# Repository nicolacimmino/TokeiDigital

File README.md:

# TokeiDigital

TokeiDigital [to̞ke̞ːdigital] is a line of clocks for geeks, nerds, and makers that come in a kit to assemble. The clock faces are unconventional and, true to the spirit of this project, always abound with colorful, blinking lights. These clocks are for you if:

* You believe a UART is a cool interface to setup a clock.
* You believe setting registers HEX values in a terminal is a good way to change LED colors and tweak settings.
* You believe a clock that just shows time with two hands is boring.

All models come with full schematics, PBCs, source code and all tools needed to program the clock. The project is OSHWA certified (PL000019).

Additionally you can buy them as kits ready to assemble on Tindie: https://www.tindie.com/stores/nicola_cimmino/

### Models

|Model|Description|Time|Date|DST|LEDs|Movement|
|-----|-----------|--------|----|---|----|----|
| [TD-FBUH01](board/TD-FBUH01) |Reproduction of the iconic Berlin Uhr.|X||X*1|36 RGB|TD-M5037|
| [TD-FDCF01](board/TD-FDCF01) |60 LEDs display time encoded as DCF77 bitstream.|X|X|X|60 RGB|TD-M5037|

<sub>*1) How can DST work if there's no date? The movment, internally, tracks the date, but the clock face doesn't have LEDs to show it. For DST Auto to work correctly you will need to set the date using the serial interface.</sub>

### Movements

|Model|Description|UART|Backup<br>Battery|W (mm)|H (mm)|
|-----|-----------|--------|----|---|----|
| [TD-M5037](board/TD-M5037)|Basic but powerful movement.|X|CR2032|50|37|

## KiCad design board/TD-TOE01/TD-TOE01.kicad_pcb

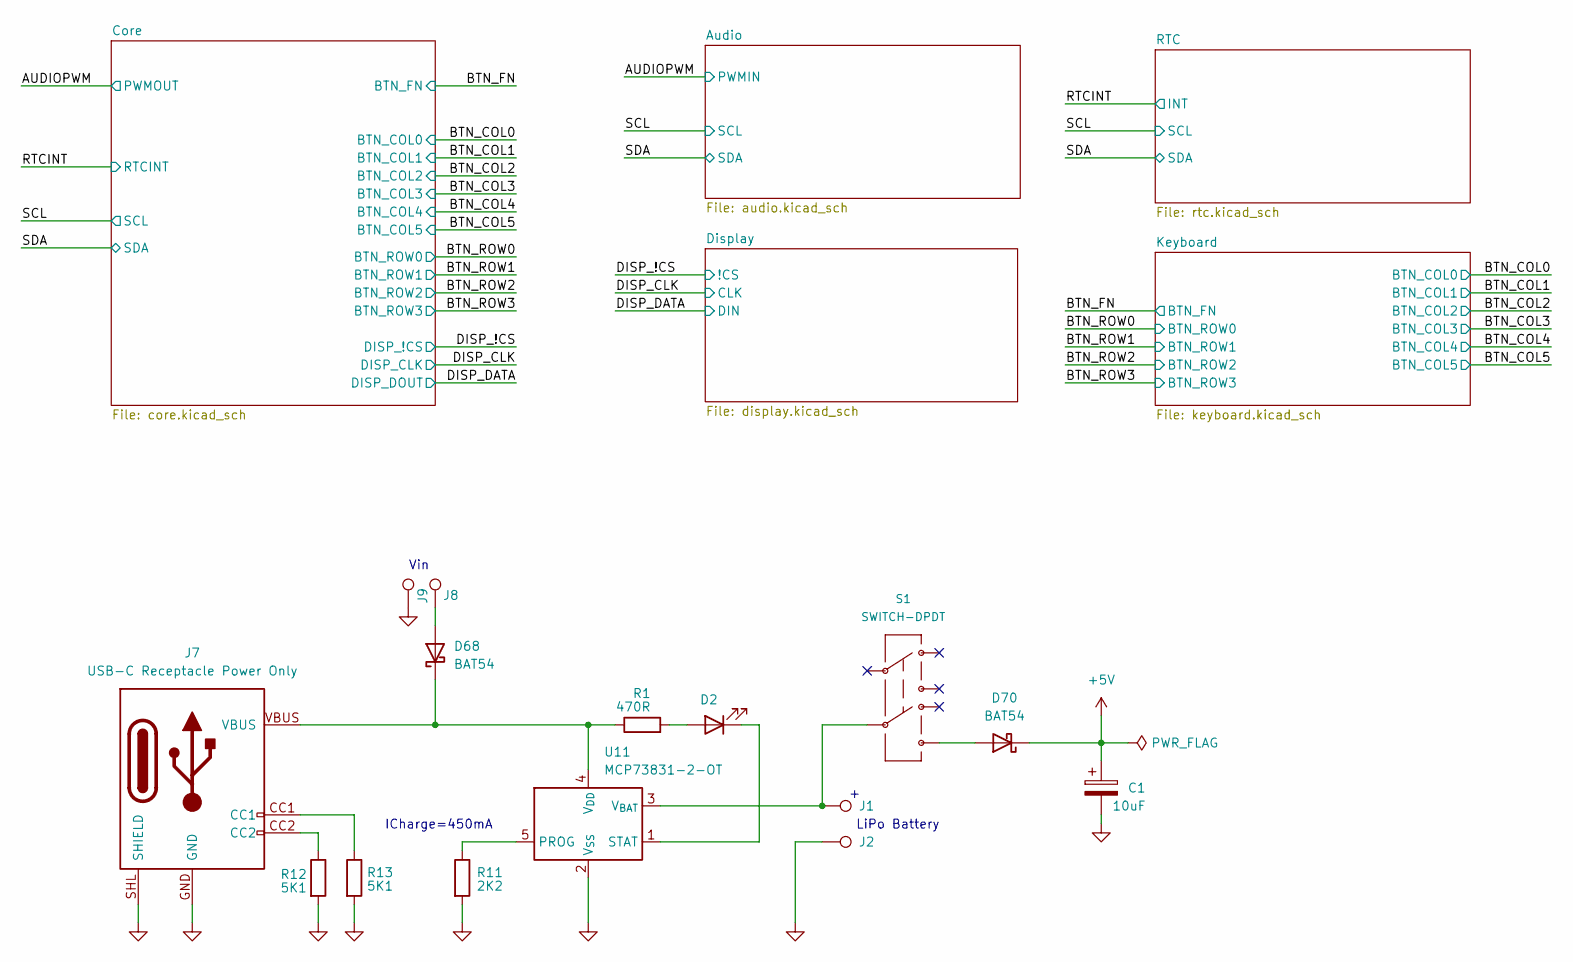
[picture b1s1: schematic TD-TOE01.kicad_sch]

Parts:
C1: 10uF; C_1206
D2: LED1206; LED_1206_3216Metric
D68, D70: BAT54; TSOT-23
J1, J8: BAT+; Power Pin
J2, J9: BAT-; Power Pin
J7: USB-C Receptacle Power Only; AMPHENOL_12402012E212A
R1: 470R; R_0805
R11: 2K2; R_0805
R12, R13: 5K1; R_0805
S1: SWITCH-DPDT; SW_DPDT_SMD_MINI
U11: MCP73831-2-OT; SOT-23-5

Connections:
+5V: C1.1, D70.3 (K); also elsewhere on the board
GND: C1.2, J2.1, J7.GND, J7.SHL (SHIELD), J9.1, R11.2, R12.2, R13.2, U11.2 (V_{SS}); also elsewhere on the board
unnamed: D2.2 (A), R1.2
unnamed: D2.1 (K), U11.1 (STAT)
unnamed: D68.1 (A), J8.1
unnamed: D68.3 (K), J7.VBUS, R1.1, U11.4 (V_{DD})
unnamed: D70.1 (A), S1.6
unnamed: J7.CC1, R13.1
unnamed: J7.CC2, R12.1
unnamed: R11.1, U11.5 (PROG)
unnamed: J1.1, S1.5, U11.3 (V_{BAT})

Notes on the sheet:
Vin
ICharge=450mA
LiPo Battery

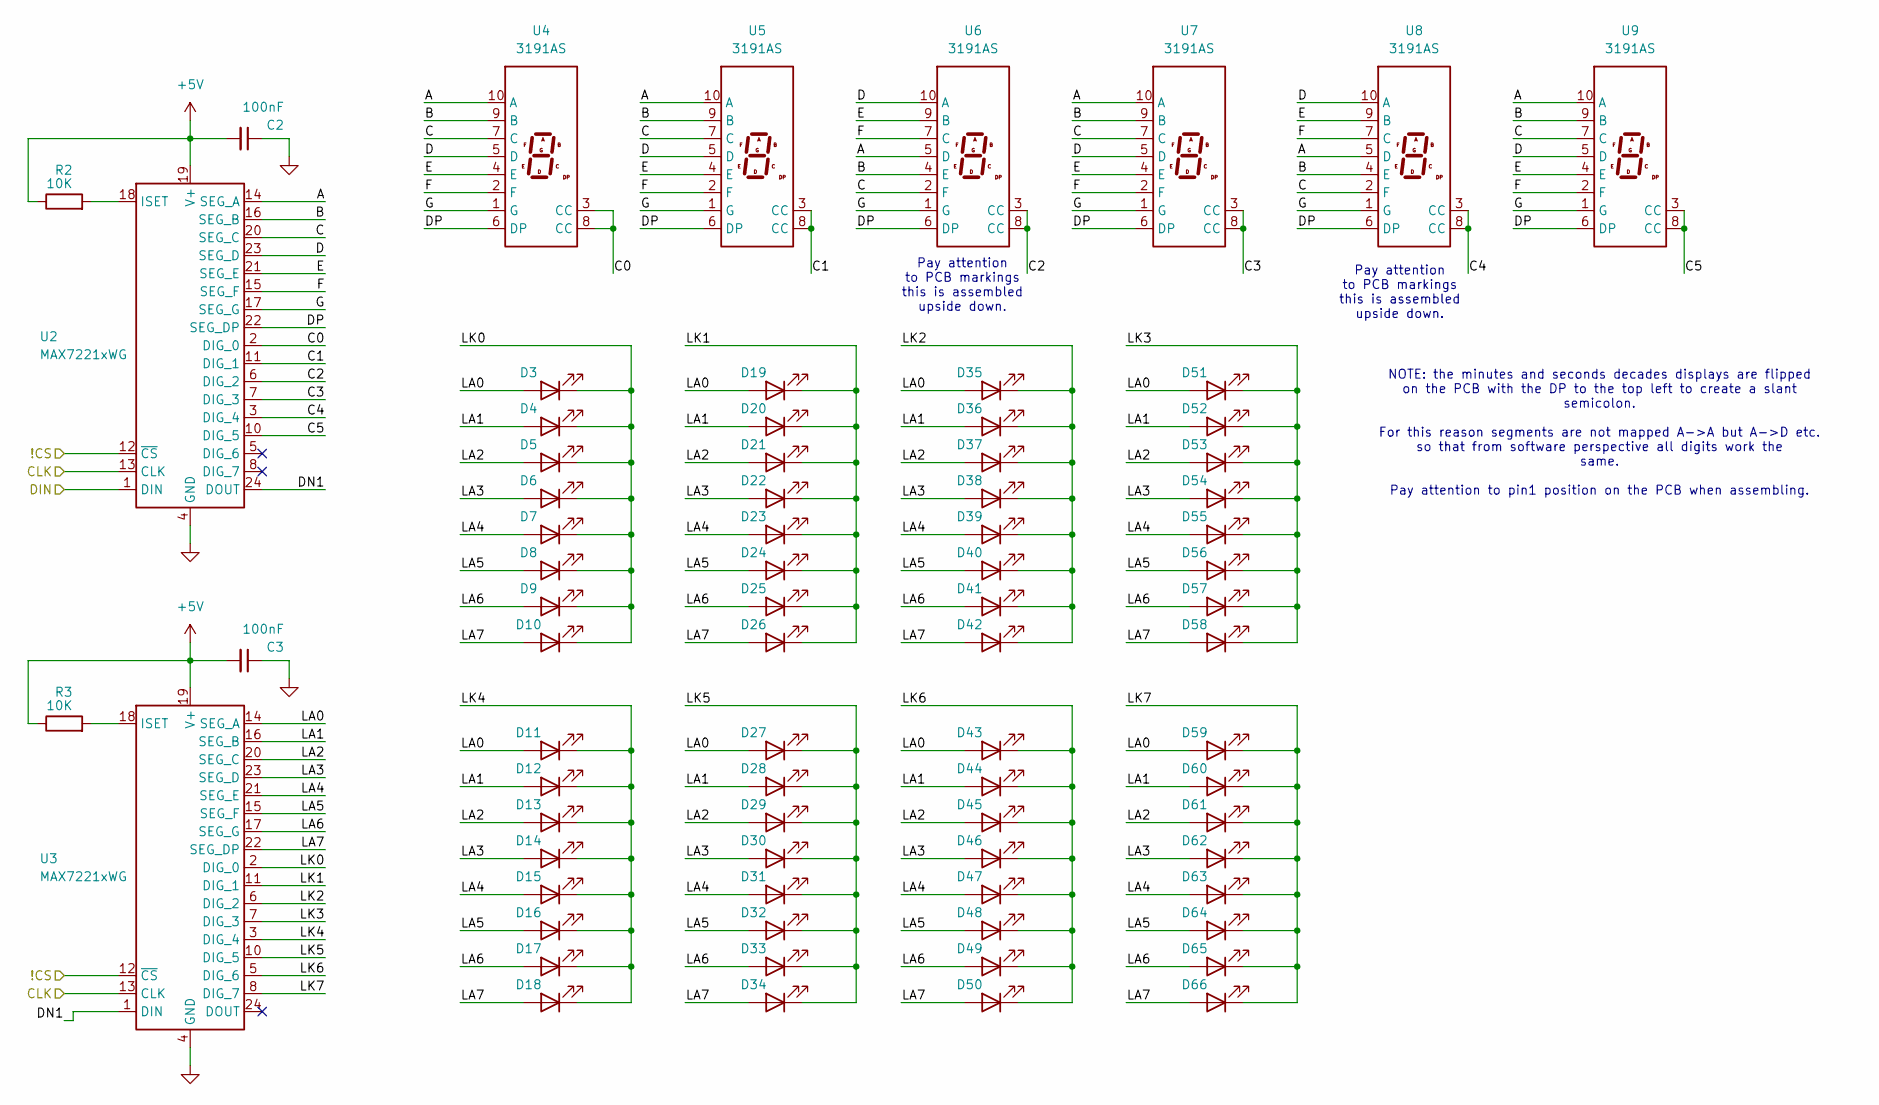
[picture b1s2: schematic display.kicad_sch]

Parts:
C2, C3: 100nF; C_1206
D3, D4, D5, D6, D7, D8, D9, D10, D11, D12, D13, D14, D15, D16, D17, D18, D19, D20, D21, D22, D23, D24, D25, D26, D27, D28, D29, D30, D31, D32, D33, D34, D35, D36, D37, D38, D39, D40, D41, D42, D43, D44, D45, D46, D47, D48, D49, D50, D51, D52, D53, D54, D55, D56, D57, D58, D59, D60, D61, D62, D63, D64, D65, D66: LED1206; LED_1206_3216Metric
R2, R3: 10K; R_0805
U2, U3: MAX7221xWG; SOIC-24W_7.5x15.4mm_P1.27mm
U4, U5, U6, U7, U8, U9: 3191AS

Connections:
+5V: C2.2, C3.2, R2.1, R3.1, U2.19 (V+), U3.19 (V+); also elsewhere on the board
/DISP_!CS: U2.12 (~CS), U3.12 (~CS); also elsewhere on the board
/DISP_CLK: U2.13 (CLK), U3.13 (CLK); also elsewhere on the board
/DISP_DATA: U2.1 (DIN); also elsewhere on the board
/Display/A: U2.14 (SEG_A), U4.10 (A), U5.10 (A), U6.5 (D), U7.10 (A), U8.5 (D), U9.10 (A)
/Display/B: U2.16 (SEG_B), U4.9 (B), U5.9 (B), U6.4 (E), U7.9 (B), U8.4 (E), U9.9 (B)
/Display/C: U2.20 (SEG_C), U4.7 (C), U5.7 (C), U6.2 (F), U7.7 (C), U8.2 (F), U9.7 (C)
/Display/C0: U2.2 (DIG_0), U4.3 (CC), U4.8 (CC)
/Display/C1: U2.11 (DIG_1), U5.3 (CC), U5.8 (CC)
/Display/C2: U2.6 (DIG_2), U6.3 (CC), U6.8 (CC)
/Display/C3: U2.7 (DIG_3), U7.3 (CC), U7.8 (CC)
/Display/C4: U2.3 (DIG_4), U8.3 (CC), U8.8 (CC)
/Display/C5: U2.10 (DIG_5), U9.3 (CC), U9.8 (CC)
/Display/D: U2.23 (SEG_D), U4.5 (D), U5.5 (D), U6.10 (A), U7.5 (D), U8.10 (A), U9.5 (D)
/Display/DN1: U2.24 (DOUT), U3.1 (DIN)
/Display/DP: U2.22 (SEG_DP), U4.6 (DP), U5.6 (DP), U6.6 (DP), U7.6 (DP), U8.6 (DP), U9.6 (DP)
/Display/E: U2.21 (SEG_E), U4.4 (E), U5.4 (E), U6.9 (B), U7.4 (E), U8.9 (B), U9.4 (E)
/Display/F: U2.15 (SEG_F), U4.2 (F), U5.2 (F), U6.7 (C), U7.2 (F), U8.7 (C), U9.2 (F)
/Display/G: U2.17 (SEG_G), U4.1 (G), U5.1 (G), U6.1 (G), U7.1 (G), U8.1 (G), U9.1 (G)
/Display/LA0: D3.2 (A), D11.2 (A), D19.2 (A), D27.2 (A), D35.2 (A), D43.2 (A), D51.2 (A), D59.2 (A), U3.14 (SEG_A)
/Display/LA1: D4.2 (A), D12.2 (A), D20.2 (A), D28.2 (A), D36.2 (A), D44.2 (A), D52.2 (A), D60.2 (A), U3.16 (SEG_B)
/Display/LA2: D5.2 (A), D13.2 (A), D21.2 (A), D29.2 (A), D37.2 (A), D45.2 (A), D53.2 (A), D61.2 (A), U3.20 (SEG_C)
/Display/LA3: D6.2 (A), D14.2 (A), D22.2 (A), D30.2 (A), D38.2 (A), D46.2 (A), D54.2 (A), D62.2 (A), U3.23 (SEG_D)
/Display/LA4: D7.2 (A), D15.2 (A), D23.2 (A), D31.2 (A), D39.2 (A), D47.2 (A), D55.2 (A), D63.2 (A), U3.21 (SEG_E)
/Display/LA5: D8.2 (A), D16.2 (A), D24.2 (A), D32.2 (A), D40.2 (A), D48.2 (A), D56.2 (A), D64.2 (A), U3.15 (SEG_F)
/Display/LA6: D9.2 (A), D17.2 (A), D25.2 (A), D33.2 (A), D41.2 (A), D49.2 (A), D57.2 (A), D65.2 (A), U3.17 (SEG_G)
/Display/LA7: D10.2 (A), D18.2 (A), D26.2 (A), D34.2 (A), D42.2 (A), D50.2 (A), D58.2 (A), D66.2 (A), U3.22 (SEG_DP)
/Display/LK0: D3.1 (K), D4.1 (K), D5.1 (K), D6.1 (K), D7.1 (K), D8.1 (K), D9.1 (K), D10.1 (K), U3.2 (DIG_0)
/Display/LK1: D19.1 (K), D20.1 (K), D21.1 (K), D22.1 (K), D23.1 (K), D24.1 (K), D25.1 (K), D26.1 (K), U3.11 (DIG_1)
/Display/LK2: D35.1 (K), D36.1 (K), D37.1 (K), D38.1 (K), D39.1 (K), D40.1 (K), D41.1 (K), D42.1 (K), U3.6 (DIG_2)
/Display/LK3: D51.1 (K), D52.1 (K), D53.1 (K), D54.1 (K), D55.1 (K), D56.1 (K), D57.1 (K), D58.1 (K), U3.7 (DIG_3)
/Display/LK4: D11.1 (K), D12.1 (K), D13.1 (K), D14.1 (K), D15.1 (K), D16.1 (K), D17.1 (K), D18.1 (K), U3.3 (DIG_4)
/Display/LK5: D27.1 (K), D28.1 (K), D29.1 (K), D30.1 (K), D31.1 (K), D32.1 (K), D33.1 (K), D34.1 (K), U3.10 (DIG_5)
/Display/LK6: D43.1 (K), D44.1 (K), D45.1 (K), D46.1 (K), D47.1 (K), D48.1 (K), D49.1 (K), D50.1 (K), U3.5 (DIG_6)
/Display/LK7: D59.1 (K), D60.1 (K), D61.1 (K), D62.1 (K), D63.1 (K), D64.1 (K), D65.1 (K), D66.1 (K), U3.8 (DIG_7)
GND: C2.1, C3.1, U2.4 (GND), U2.9 (GND), U3.4 (GND), U3.9 (GND); also elsewhere on the board
unnamed: R2.2, U2.18 (ISET)
unnamed: R3.2, U3.18 (ISET)

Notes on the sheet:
Pay attention to PCB markings this is assembled upside down.
NOTE: the minutes and seconds decades displays are flipped on the PCB with the DP to the top left to create a slant semicolon. For this reason segments are not mapped A->A but A->D etc. so that from software perspective all digits work the same. Pay attention to pin1 position on the PCB when assemb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

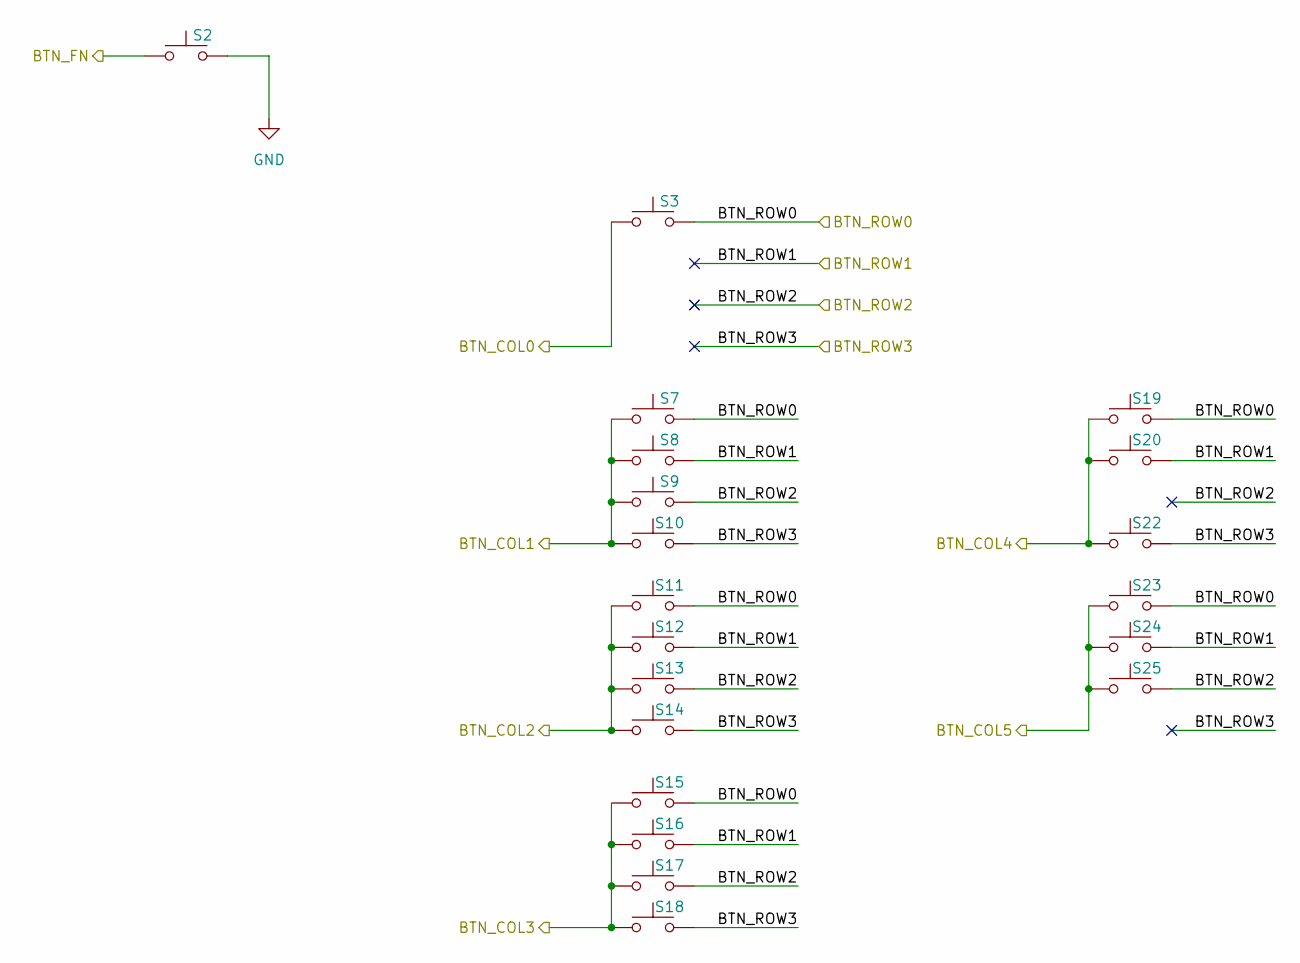
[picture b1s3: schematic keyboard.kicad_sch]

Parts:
S2, S3, S7, S8, S9, S10, S11, S12, S13, S14, S15, S16, S17, S18, S19, S20, S22, S23, S24, S25: Push Button; Tactile SW SMD

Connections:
/BTN_COL0: S3.1; also elsewhere on the board
/BTN_COL1: S7.1, S8.1, S9.1, S10.1; also elsewhere on the board
/BTN_COL2: S11.1, S12.1, S13.1, S14.1; also elsewhere on the board
/BTN_COL3: S15.1, S16.1, S17.1, S18.1; also elsewhere on the board
/BTN_COL4: S19.1, S20.1, S22.1; also elsewhere on the board
/BTN_COL5: S23.1, S24.1, S25.1; also elsewhere on the board
/BTN_FN: S2.1; also elsewhere on the board
/BTN_ROW0: S3.2, S7.2, S11.2, S15.2, S19.2, S23.2; also elsewhere on the board
/BTN_ROW1: S8.2, S12.2, S16.2, S20.2, S24.2; also elsewhere on the board
/BTN_ROW2: S9.2, S13.2, S17.2, S25.2; also elsewhere on the board
/BTN_ROW3: S10.2, S14.2, S18.2, S22.2; also elsewhere on the board
GND: S2.2; also elsewhere on the board

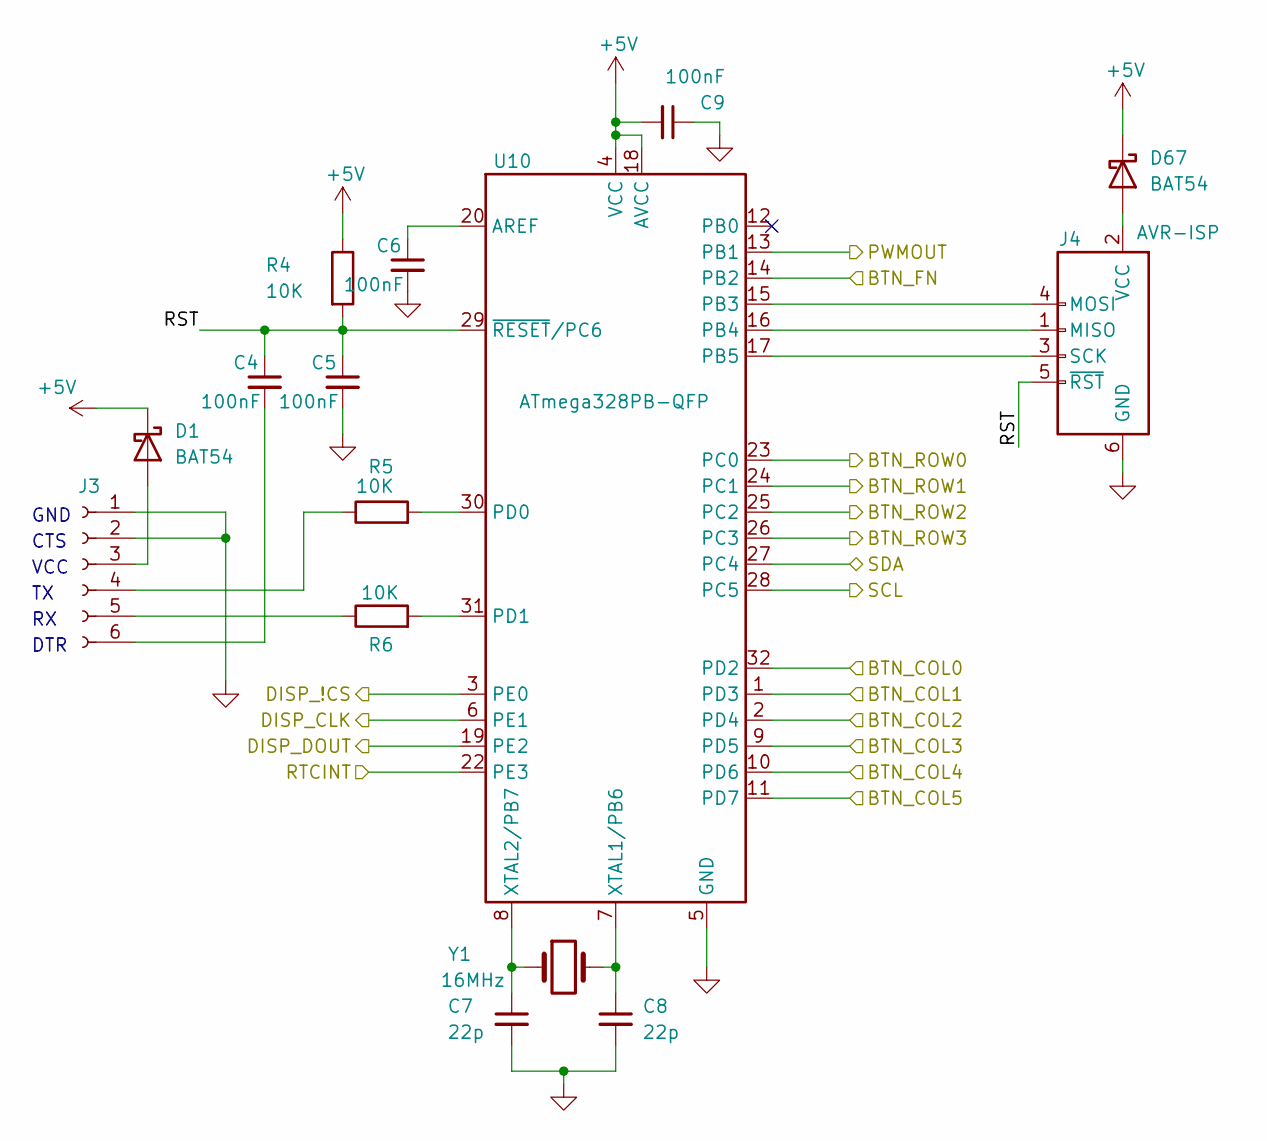
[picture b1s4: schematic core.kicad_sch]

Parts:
C4, C5, C6, C9: 100nF; C_1206
C7, C8: 22p; C_1206
D1, D67: BAT54; TSOT-23
J3: Pin 1x6; PinSocket_1x06_P2.54mm_Horizontal
J4: AVR-ISP; PIN 2x03
R4, R5, R6: 10K; R_0805
U10: ATmega328PB-QFP; TQFP-32_7x7mm_P0.8mm
Y1: 16MHz; Crystal_SMD_HC49-SD_HandSoldering

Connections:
+5V: C9.2, D1.3 (K), D67.3 (K), R4.1, U10.4 (VCC), U10.18 (AVCC); also elsewhere on the board
/AUDIOPWM: U10.13 (PB1); also elsewhere on the board
/BTN_COL0: U10.32 (PD2); also elsewhere on the board
/BTN_COL1: U10.1 (PD3); also elsewhere on the board
/BTN_COL2: U10.2 (PD4); also elsewhere on the board
/BTN_COL3: U10.9 (PD5); also elsewhere on the board
/BTN_COL4: U10.10 (PD6); also elsewhere on the board
/BTN_COL5: U10.11 (PD7); also elsewhere on the board
/BTN_FN: U10.14 (PB2); also elsewhere on the board
/BTN_ROW0: U10.23 (PC0); also elsewhere on the board
/BTN_ROW1: U10.24 (PC1); also elsewhere on the board
/BTN_ROW2: U10.25 (PC2); also elsewhere on the board
/BTN_ROW3: U10.26 (PC3); also elsewhere on the board
/Core/RST: C4.1, C5.1, J4.5 (~RST), R4.2, U10.29 (~RESET/PC6)
/DISP_!CS: U10.3 (PE0); also elsewhere on the board
/DISP_CLK: U10.6 (PE1); also elsewhere on the board
/DISP_DATA: U10.19 (PE2); also elsewhere on the board
/RTCINT: U10.22 (PE3); also elsewhere on the board
/SCL: U10.28 (PC5); also elsewhere on the board
/SDA: U10.27 (PC4); also elsewhere on the board
GND: C5.2, C6.2, C7.2, C8.2, C9.1, J3.1, J3.2, J4.6 (GND), U10.5 (GND), U10.21 (GND); also elsewhere on the board
unnamed: D1.1 (A), J3.3
unnamed: D67.1 (A), J4.2 (VCC)
unnamed: J3.4, R5.1
unnamed: J3.5, R6.1
unnamed: C4.2, J3.6
unnamed: J4.1 (MISO), U10.16 (PB4)
unnamed: J4.4 (MOSI), U10.15 (PB3)
unnamed: J4.3 (SCK), U10.17 (PB5)
unnamed: C6.1, U10.20 (AREF)
unnamed: R5.2, U10.30 (PD0)
unnamed: R6.2, U10.31 (PD1)
unnamed: C8.1, U10.7 (XTAL1/PB6), Y1.2
unnamed: C7.1, U10.8 (XTAL2/PB7), Y1.1

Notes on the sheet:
VCC
CTS
DTR
GND

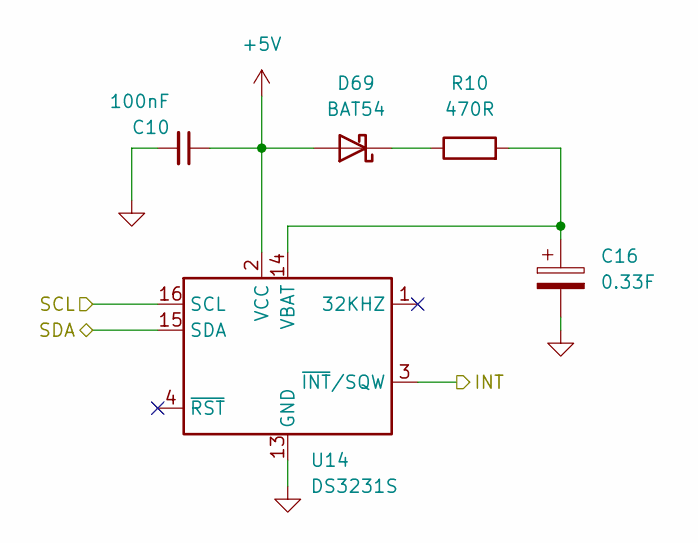
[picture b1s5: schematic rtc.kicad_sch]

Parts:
C10: 100nF; C_1206
C16: 0.33F; StarcapSuperCap-HType
D69: BAT54; TSOT-23
R10: 470R; R_0805
U14: DS3231S; SOIC-16W_7.5x10.3mm_P1.27mm

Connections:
+5V: C10.1, D69.1 (A), U14.2 (VCC); also elsewhere on the board
/RTCINT: U14.3 (~INT/SQW); also elsewhere on the board
/SCL: U14.16 (SCL); also elsewhere on the board
/SDA: U14.15 (SDA); also elsewhere on the board
GND: C10.2, C16.2, U14.5 (GND), U14.6 (GND), U14.7 (GND), U14.8 (GND), U14.9 (GND), U14.10 (GND), U14.11 (GND), U14.12 (GND), U14.13 (GND); also elsewhere on the board
unnamed: D69.3 (K), R10.1
unnamed: C16.1, R10.2, U14.14 (VBAT)

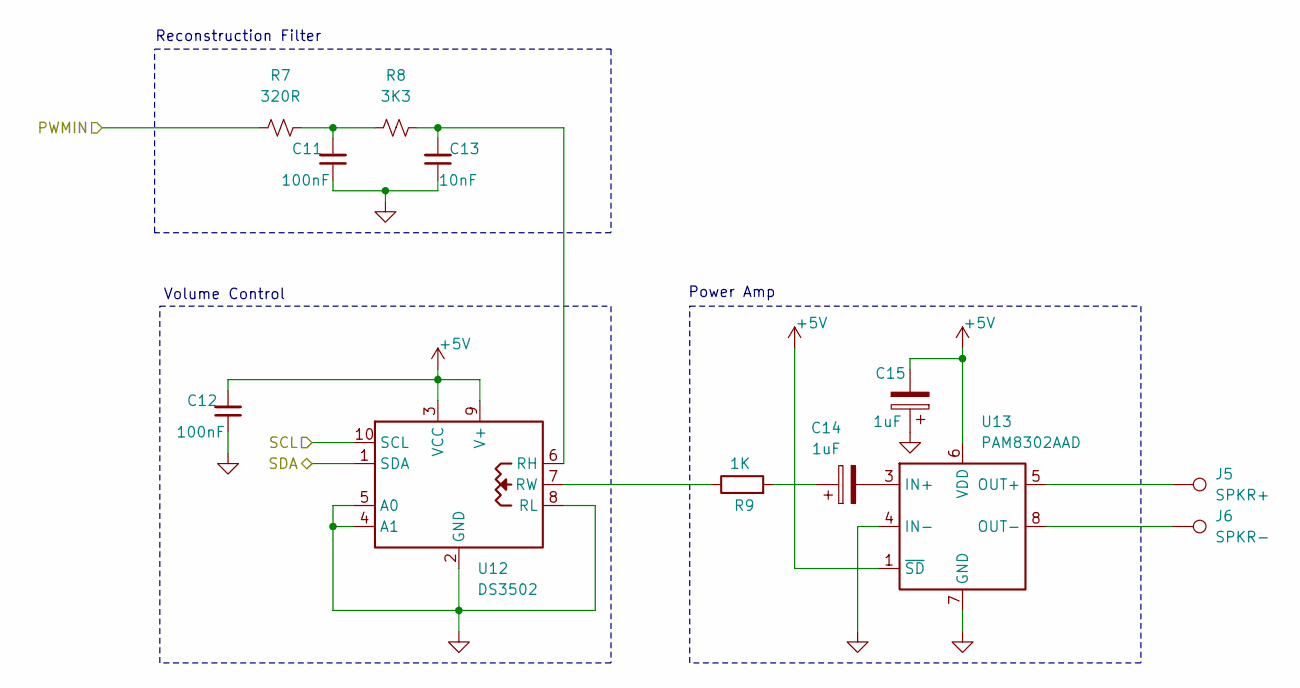
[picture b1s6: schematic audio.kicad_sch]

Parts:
C11, C12: 100nF; C_1206
C13: 10nF; C_1206
C14, C15: 1uF; C_1206
J5: SPKR+; Power Pin
J6: SPKR-; Power Pin
R7: 320R; R_0805
R8: 3K3; R_0805
R9: 1K; R_0805
U12: DS3502; MSOP-10_3x3mm_P0.5mm
U13: PAM8302AAD; MSOP-8_3x3mm_P0.65mm

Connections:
+5V: C12.2, C15.2, U12.3 (VCC), U12.9 (V+), U13.1 (~SD), U13.6 (VDD); also elsewhere on the board
/AUDIOPWM: R7.2; also elsewhere on the board
/SCL: U12.10 (SCL); also elsewhere on the board
/SDA: U12.1 (SDA); also elsewhere on the board
GND: C11.1, C12.1, C13.1, C15.1, U12.2 (GND), U12.4 (A1), U12.5 (A0), U12.8 (RL), U13.4 (IN-), U13.7 (GND); also elsewhere on the board
unnamed: C11.2, R7.1, R8.2
unnamed: C14.1, R9.2
unnamed: C13.2, R8.1, U12.6 (RH)
unnamed: R9.1, U12.7 (RW)
unnamed: C14.2, U13.3 (IN+)
unnamed: J5.1, U13.5 (OUT+)
unnamed: J6.1, U13.8 (OUT-)

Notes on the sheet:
Reconstruction Filter
Volume Control
Power Amp

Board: 2 copper layers, 143 parts (52 on the bottom side), 85 nets, no tracks yet.

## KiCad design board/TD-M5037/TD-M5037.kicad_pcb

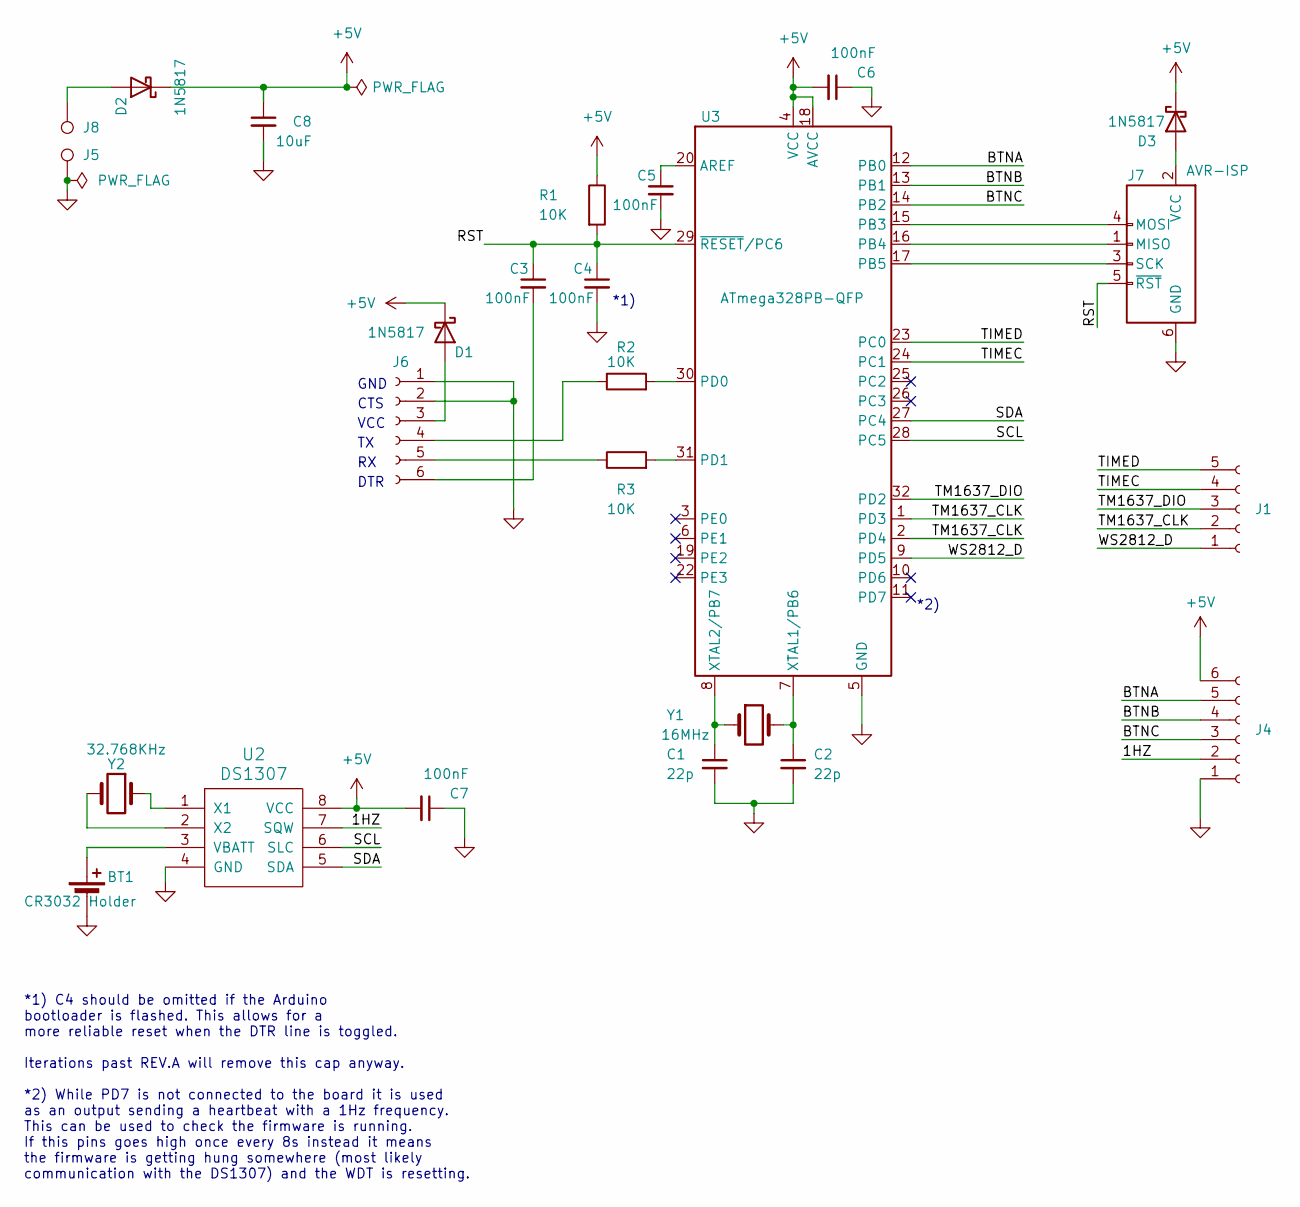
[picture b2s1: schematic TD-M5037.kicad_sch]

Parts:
BT1: CR3032 Holder; CR2032 Holder
C1, C2: 22p; C_0805
C3, C4, C5, C6, C7: 100nF; C_0805
C8: 10uF; C_1206
D1, D2, D3: 1N5817; D_2010
J1: Pin 1x5; PIN 1x05
J4, J6: Pin 1x6; PIN 1x06
J5, J8: PowerPad; Power Pin
J7: AVR-ISP; PIN 2x03
R1, R2, R3: 10K; R_0805
U2: DS1307; SOIC-8
U3: ATmega328PB-QFP; TQFP-32
Y1: 16MHz; Crystal Vertical
Y2: 32.768KHz; Crystal Horizontal

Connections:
+5V: C6.2, C7.2, C8.1, D1.1 (K), D2.1 (K), D3.1 (K), J4.6, R1.1, U2.8 (VCC), U3.4 (VCC), U3.18 (AVCC)
/1HZ: J4.2, U2.7 (SQW)
/BTNA: J4.5, U3.12 (PB0)
/BTNB: J4.4, U3.13 (PB1)
/BTNC: J4.3, U3.14 (PB2)
/RST: C3.1, C4.1, J7.5 (~RST), R1.2, U3.29 (~RESET/PC6)
/SCL: U2.6 (SLC), U3.28 (PC5)
/SDA: U2.5 (SDA), U3.27 (PC4)
/TIMEC: J1.4, U3.24 (PC1)
/TIMED: J1.5, U3.23 (PC0)
/TM1637_CLK: J1.2, U3.1 (PD3), U3.2 (PD4)
/TM1637_DIO: J1.3, U3.32 (PD2)
/WS2812_D: J1.1, U3.9 (PD5)
GND: BT1.2 (-), C1.2, C2.2, C4.2, C5.2, C6.1, C7.1, C8.2, J4.1, J5.1, J6.1, J6.2, J7.6 (GND), U2.4 (GND), U3.5 (GND), U3.21 (GND)
unnamed: BT1.1 (+), U2.3 (VBATT)
unnamed: D1.2 (A), J6.3
unnamed: D2.2 (A), J8.1
unnamed: D3.2 (A), J7.2 (VCC)
unnamed: J6.4, R2.1
unnamed: J6.5, R3.1
unnamed: C3.2, J6.6
unnamed: J7.1 (MISO), U3.16 (PB4)
unnamed: J7.4 (MOSI), U3.15 (PB3)
unnamed: J7.3 (SCK), U3.17 (PB5)
unnamed: U2.1 (X1), Y2.1
unnamed: U2.2 (X2), Y2.2
unnamed: C5.1, U3.20 (AREF)
unnamed: R2.2, U3.30 (PD0)
unnamed: R3.2, U3.31 (PD1)
unnamed: C2.1, U3.7 (XTAL1/PB6), Y1.2
unnamed: C1.1, U3.8 (XTAL2/PB7), Y1.1

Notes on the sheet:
*1) C4 should be omitted if the Arduino bootloader is flashed. This allows for a more reliable reset when the DTR line is toggled. Iterations past REV.A will remove this cap anyway. *2) While PD7 is not connected to the board it is used as an output sending a heartbeat with a 1Hz frequency. This ca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
*1)
DTR
GND
VCC
*2)
CTS

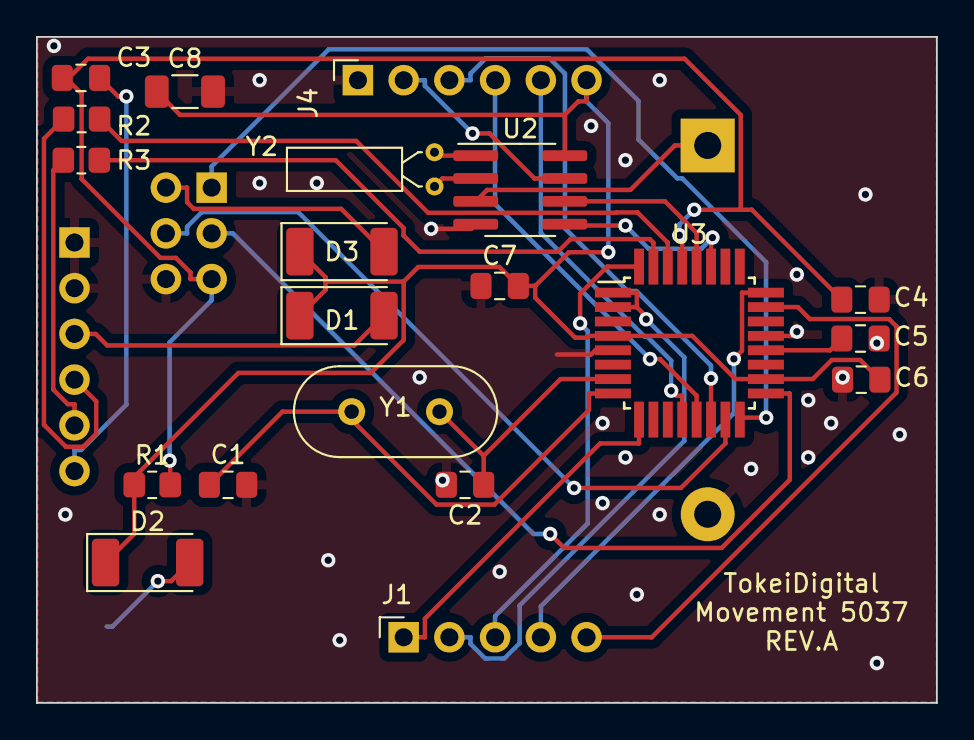
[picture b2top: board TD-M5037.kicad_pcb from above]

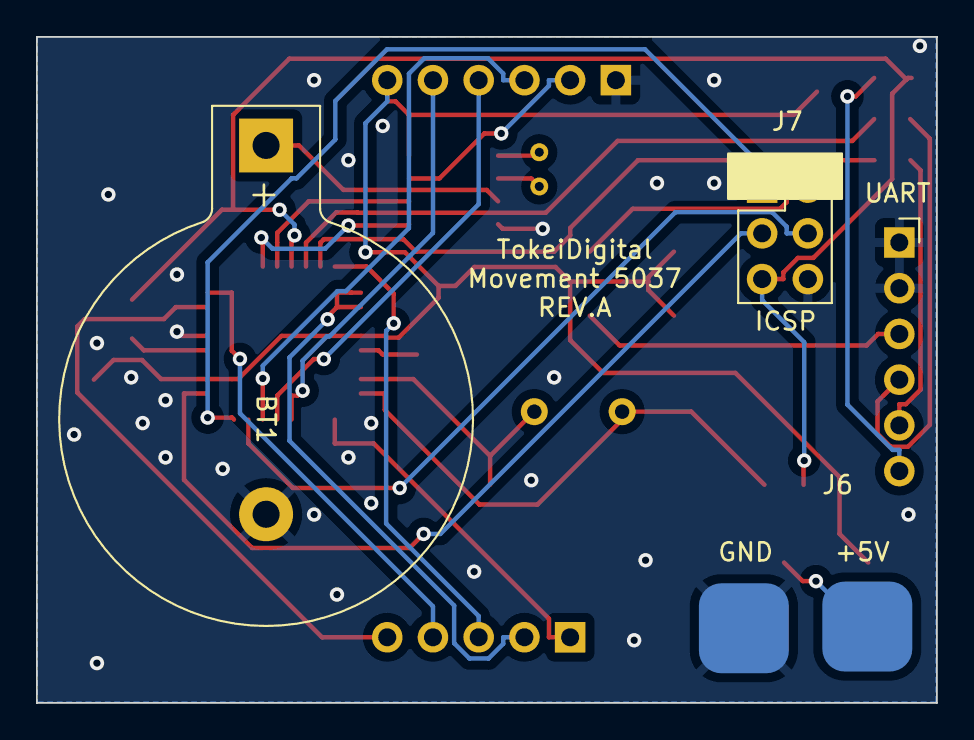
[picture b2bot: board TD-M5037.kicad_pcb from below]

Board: 2 copper layers, 50.0 x 37.0 mm, 25 parts (5 on the bottom side), 31 nets.
